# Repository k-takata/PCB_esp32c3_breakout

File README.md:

# ESP32-C3-WROOM-02 Breakout Board

## 概要

[ESP32-C3-WROOM-02](https://akizukidenshi.com/catalog/g/g117493/)を2.54mmピッチに変換するための基板です。

秋月電子の[AE-ESP-WROOM-02](https://akizukidenshi.com/catalog/g/g109715)は一部のピンがGNDに接続されているため、そのままではESP32-C3-WROOM-02に使うことはできません。[改造](https://twitter.com/k_takata/status/1746381656318157104)すれば使えなくもないですが、面倒な上にピン名も異なっていて間違えやすいため、ESP32-C3-WROOM-02用の基板を作成しました。

ESP32-C3-WROOM-02を使う上で必須のEN端子のプルアップ抵抗も基板上に実装することができるようになっています。

## 使用したソフトウェア

KiCad 7.0

## 回路図

## 基板パターン図

4層基板になっています。

## 部品表

| Reference           |個数|値    | 説明 |
|---------------------|----|------|------|
|R1                   |   1| 10kΩ|EN端子プルアップ抵抗、2012サイズ|
|U1                   |   1|[ESP32-C3-WROOM-02-N4](https://akizukidenshi.com/catalog/g/g117493/)|Wi-Fi モジュール|
|J1, J2               |   2|-     |[細ピンヘッダー](https://akizukidenshi.com/catalog/r/rsheader) 1x9、あるいは[丸ピンIC用連結ソケット](https://akizukidenshi.com/catalog/goods/search.aspx?keyword=%E9%80%A3%E7%B5%90%E3%82%BD%E3%82%B1%E3%83%83%E3%83%88&ct=040201&search=%E6%A4%9C%E7%B4%A2%E3%81%99%E3%82%8B) 1x9、あるいは[リードフレーム](https://akizukidenshi.com/catalog/g/g114883/) 1x9|

## 完成品

## License

CC0

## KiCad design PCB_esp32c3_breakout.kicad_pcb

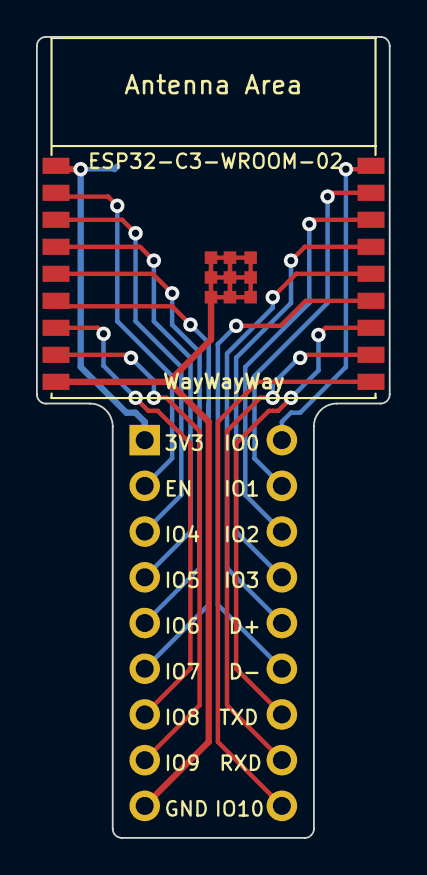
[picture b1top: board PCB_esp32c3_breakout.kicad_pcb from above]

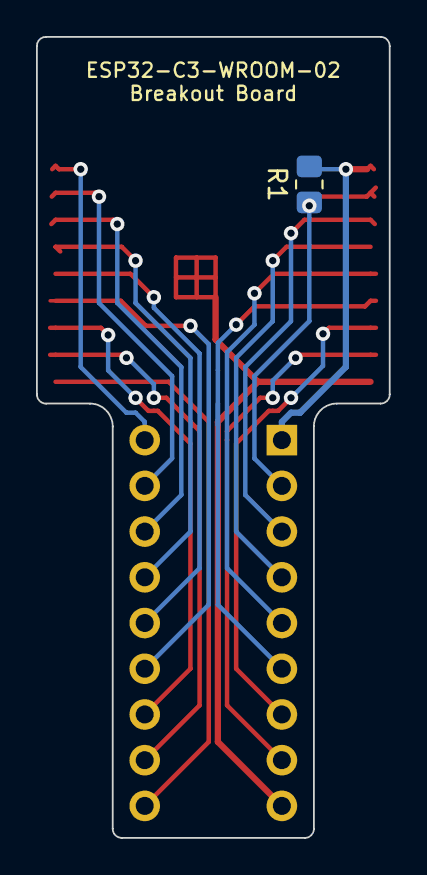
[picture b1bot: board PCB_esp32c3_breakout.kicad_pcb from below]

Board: 2 copper layers, 19.6 x 44.5 mm, 4 parts (3 on the bottom side), 18 nets.

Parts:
J1, J2: Conn_01x09_Pin; PinHeader_1x09_P2.54mm_Vertical
R1: 10k; R_0805_2012Metric_Pad1.20x1.40mm_HandSolder
U1: ESP32-C3-WROOM-02

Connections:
+3.3V: J1.1, R1.1, U1.1 (3V3)
EN: J1.2, R1.2, U1.2 (EN/CHIP_PU)
GND: J1.9, U1.9 (GND), U1.19 (GND)
GPIO0: J2.9, U1.18 (GPIO0/ADC1_CH0/XTAL_32K_P)
GPIO1: J2.8, U1.17 (GPIO1/ADC1_CH1/XTAL_32K_N)
GPIO2: J2.7, U1.16 (GPIO2/ADC1_CH2)
GPIO3: J2.6, U1.15 (GPIO3/ADC1_CH3)
GPIO4: J1.3, U1.3 (GPIO4/ADC1_CH4)
GPIO5: J1.4, U1.4 (GPIO5/ADC2_CH0)
GPIO6: J1.5, U1.5 (GPIO6)
GPIO7: J1.6, U1.6 (GPIO7)
GPIO8: J1.7, U1.7 (GPIO8)
GPIO9: J1.8, U1.8 (GPIO9)
GPIO10: J2.1, U1.10 (GPIO10)
U0RXD: J2.2, U1.11 (GPIO20/U0RXD)
U0TXD: J2.3, U1.12 (GPIO21/U0TXD)
USB_D+: J2.5, U1.14 (GPIO19/USB_D+)
USB_D-: J2.4, U1.13 (GPIO18/USB_D-)

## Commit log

2024-02-10 First version
2024-02-10 Update PCB to Rev. 1.1
    4層基板に変更。
2024-02-10 Change thickness from 1.6mm to 1.2mm
2024-02-23 Adjust board size
2024-02-23 完成品の写真を追加
2024-03-06 Change JLCJLCJLCJLC to WayWayWay
2025-06-30 Update README
    Update links.
